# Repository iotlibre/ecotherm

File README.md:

ecoTherm
==========
ecoThermal esta diseñado para medir la energía térmica de una instalación que disponga de uno o varios circuitos de agua a diferentes temperaturas. Este dispositivo esta diseñado para medir:

* Temperatura mediante sondas del tipo 18b20
* Caudal a través de pulsos proporcionados por contadores de agua
* Valores analógicos tanto de voltaje como de corriente. 

Las medias se toman cada segundo haciendo una media de estos valores para cada periodo de reporte en el que el valor es proporcionado.

ecoThermal se puede instalar sobre carril DIN a una distancia que permita la comunicación con las sondas disponibles en la instalación. En un edificio podemos tener tantos dispositivos como sean necesarios y el servidor los integrará en la misma instalación sin necesidad de configuraciones adicionales o cambios en el Firmware. La comunicación se hace mediante wifi por lo que no es necesario el cableado de datos al equipo solamente es preciso que esté dentro de la cobertura de la red wifi del edificio.

Para el uso de ecoThermal, no son necesarios conocimientos de informática aunque todos los desarrollos y el hardware están hechos bajo licencias libres lo que permite la modificación y mejora de las funcionalidades.

.. image:: ./imagenes/ecothermal_board.png

Principales características
---------------------------
* 15 entradas configurables para cada tipo de sensor
* Admite hasta 28 sondas de temperatura repartidas en 7 buses
* Es posible integrar hasta 15 medidas de caudal
* Puede medir hasta 8 Valores analógicos
* Precisión en las medida de temperatura: ± 0,5 °C
* La precisión de las medidas analógicas depende de las sondas utilizadas.
* La precisión de las medias de caudal corresponde a los medidores implementados
* Comunicación a Internet se hace por WIFI local
* Configurable vía Web
* Estandard: IEEE 802.11 b/g/n
* Alimentación a 220 voltios de corriente alterna. Rango: 85 ~ 264VAC
* Montaje en carril din
* La PCB integra un Arduino nano con el ESP8266 12E
* Compatible con el servidor IoE

Puesta a punto
--------------
La puesta a punto de ecoThermal consta de tres partes:

* La configuración del hardware
* El firmware de Arduino
* La configuración en la instalación

La configuración del hardware
~~~~~~~~~~~~~~~~~~~~~~~~~~~~~
El hardware por defecto esta preparado para 8 entradas analógicas, 3 caudales y 16 sondas de temperatura repartidas en 4 buses. Sin embargo esta configuración se puede modificar cambiando los componentes de superficie de la PCB hasta la combinación de medidas que nos se adapte mas al proyecto.

El firmware de Arduino
~~~~~~~~~~~~~~~~~~~~~~
El firmware que esta cargado, por defecto, en el Arduino nano funciona correctamente con la configuración, del hardware, por defecto. En el caso de cambiar el hardware también es necesario cambiar el firmware del Arduino integrado en la PCB y que se puede encontrar en el código fuente

La configuración en la instalación
~~~~~~~~~~~~~~~~~~~~~~~~~~~~~~~~~~
En este punto se definen los parámetros del servidor de destino y la wifi local a la que va a estar conectado el dispositivo. Con este fin, la primera vez que se ponga en servicio el ESP y siempre que no encuentre la WIFI configurada, el ESP 8266 12E creará su propio punto de acceso, su propia red WIFI. Conectándose a cualquier dirección a través de este punto de acceso nos aparecerá la página de configuración del ESP. Tengase en cuenta que una vez configurado el ESP y conectado a una red WIFI el router le asignará una única dirección IP a la que será necesario acceder para cambiar la configuración

Código fuente
~~~~~~~~~~~~~
El código del firmware y la documentación del hardware se puede encontrar en `repositorio <https://github.com/iotlibre/ecoThermal>`_

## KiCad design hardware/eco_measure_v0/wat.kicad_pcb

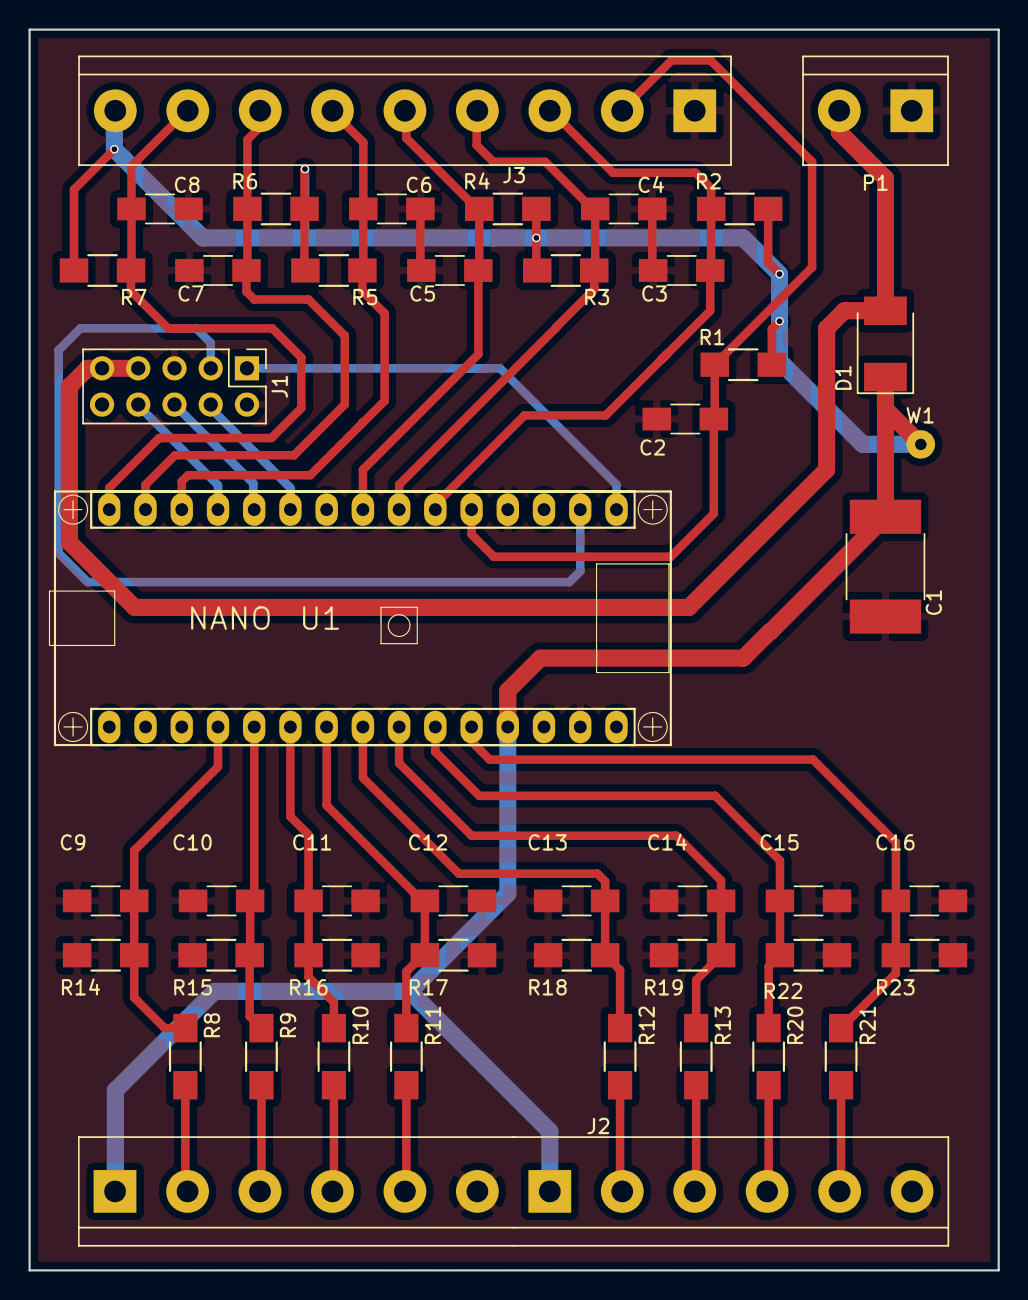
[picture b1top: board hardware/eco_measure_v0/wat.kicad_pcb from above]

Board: 2 copper layers, 67.9 x 87.0 mm, 46 parts (0 on the bottom side), 31 nets.

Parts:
C1: 10uF; C_2220_HandSoldering
C2, C3, C4, C5, C6, C7, C8, C9, C10, C11, C12, C13, C14, C15, C16: 100nF; C_1206_HandSoldering
D1: schottky; D_2114
J1: Conn_02x05_Odd_Even; Pin_Header_Straight_2x05_Pitch2.54mm_onsar
J2: Conn_01x12; TerminalBlock_bornier-12_P5.08mm
J3: Conn_01x09; TerminalBlock_bornier-9_P5.08mm
P1: V_IN; TerminalBlock_bornier-2_P5.08mm
R1, R2, R3, R4, R5, R6, R7, R8, R9, R10, R11, R12, R13, R14, R15, R16, R17, R18, R19, R20, R21, R22, R23: 10k; R_1206_HandSoldering
U1: NANO; arduino_nano
W1: +5V; SolderWirePad_single_0-8mmDrill

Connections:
/A0: C9.1, R8.1, R14.2, U1.19
/A1: C10.1, R9.1, R15.2, U1.20
/A2: C11.1, R10.1, R16.2, U1.21
/A3: C12.1, R11.1, R17.2, U1.22
/A4: C13.1, R12.1, R18.2, U1.23
/A5: C14.1, R13.1, R19.2, U1.24
/A6: C15.1, R20.1, R22.2, U1.25
/A7: C16.1, R21.1, R23.2, U1.26
/D2: C2.1, J3.2, R1.1, U1.5
/D3: C3.1, J3.3, R2.1, U1.6
/D4: C4.1, J3.4, R3.1, U1.7
/D5: C5.1, J3.5, R4.1, U1.8
/D7: J1.4, U1.10
/D8: J1.6, U1.11
/D9: J1.8, U1.12
/D10: C6.1, J3.6, R5.1, U1.13
/D11: C7.1, J3.7, R6.1, U1.14
/D12: C8.1, J3.8, R7.1, U1.15
/ard_rx: J1.3, U1.2
/ard_tx: J1.1, U1.1
/jA0: J2.2, R8.2
/jA1: J2.3, R9.2
/jA2: J2.4, R10.2
/jA3: J2.5, R11.2
/jA4: J2.8, R12.2
/jA5: J2.9, R13.2
/jA6: J2.10, R20.2
/jA7: J2.11, R21.2
/vcc_5v: D1.2, J1.7, J1.9, P1.2
GND: C1.2, C2.2, C3.2, C4.2, C5.2, C6.2, C7.2, C8.2, C9.2, C10.2, C11.2, C12.2, C13.2, C14.2, C15.2, C16.2, J1.2, J1.5, J2.6, J2.12, J3.1, P1.1, R14.1, R15.1, R16.1, R17.1, R18.1, R19.1, R22.1, R23.1, U1.4, U1.29
VCC: C1.1, D1.1, J2.1, J2.7, J3.9, R1.2, R2.2, R3.2, R4.2, R5.2, R6.2, R7.2, U1.27, W1.1

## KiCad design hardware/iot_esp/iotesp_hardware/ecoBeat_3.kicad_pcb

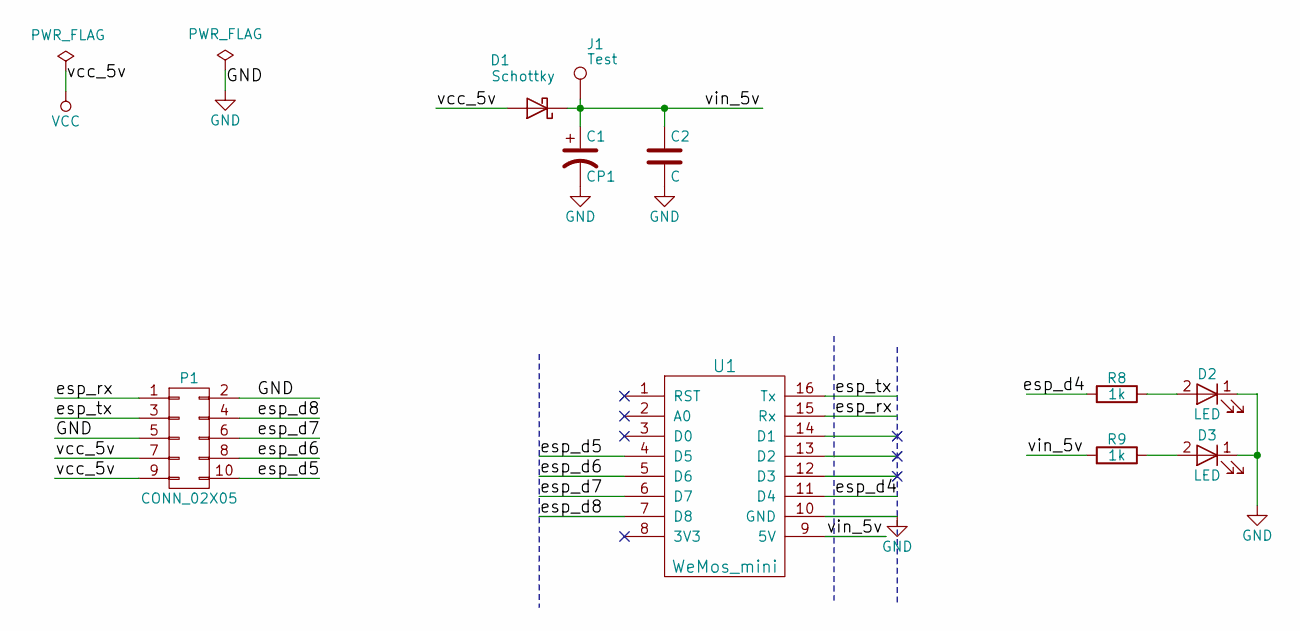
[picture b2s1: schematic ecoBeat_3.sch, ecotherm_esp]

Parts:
C1: CP1; C_2220_HandSoldering
C2: C; C_1206_HandSoldering
D1: Schottky; D_2114
D2, D3: LED; LED_D3.0mm
J1: Test; SolderWirePad_single_0-8mmDrill
P1: CONN_02X05; D1_mini_board
R8, R9: 1k; R_1206_HandSoldering
U1: WeMos_mini; D1_mini_board_oscar

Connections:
/esp_d4: R8.2, U1.11 (D4)
/esp_d5: P1.10, U1.4 (D5)
/esp_d6: P1.8, U1.5 (D6)
/esp_d7: P1.6, U1.6 (D7)
/esp_d8: P1.4, U1.7 (D8)
/esp_rx: P1.1, U1.15 (Rx)
/esp_tx: P1.3, U1.16 (Tx)
/vin_5v: C1.1, C2.1, D1.1 (K), J1.1, R9.2, U1.9 (5V)
GND: C1.2, C2.2, D2.1 (K), D3.1 (K), P1.2, P1.5, U1.10 (GND)
unnamed: D2.2 (A), R8.1
unnamed: D3.2 (A), R9.1
VCC: D1.2 (A), P1.7, P1.9

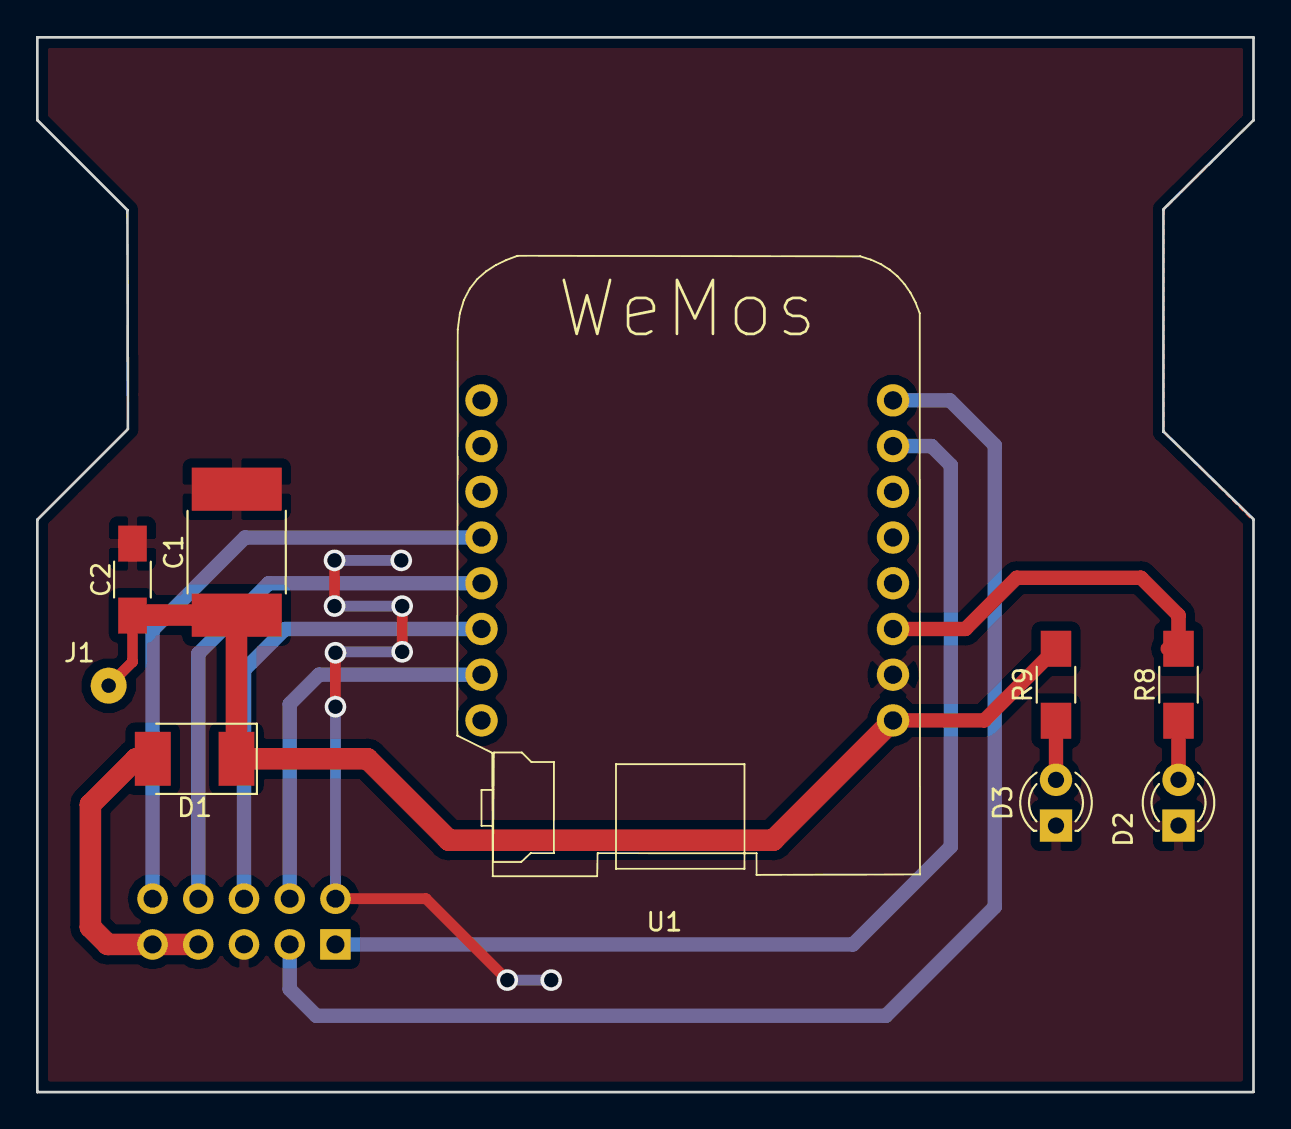
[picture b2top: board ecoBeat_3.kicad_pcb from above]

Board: 2 copper layers, 67.6 x 58.6 mm, 10 parts (1 on the bottom side), 12 nets.

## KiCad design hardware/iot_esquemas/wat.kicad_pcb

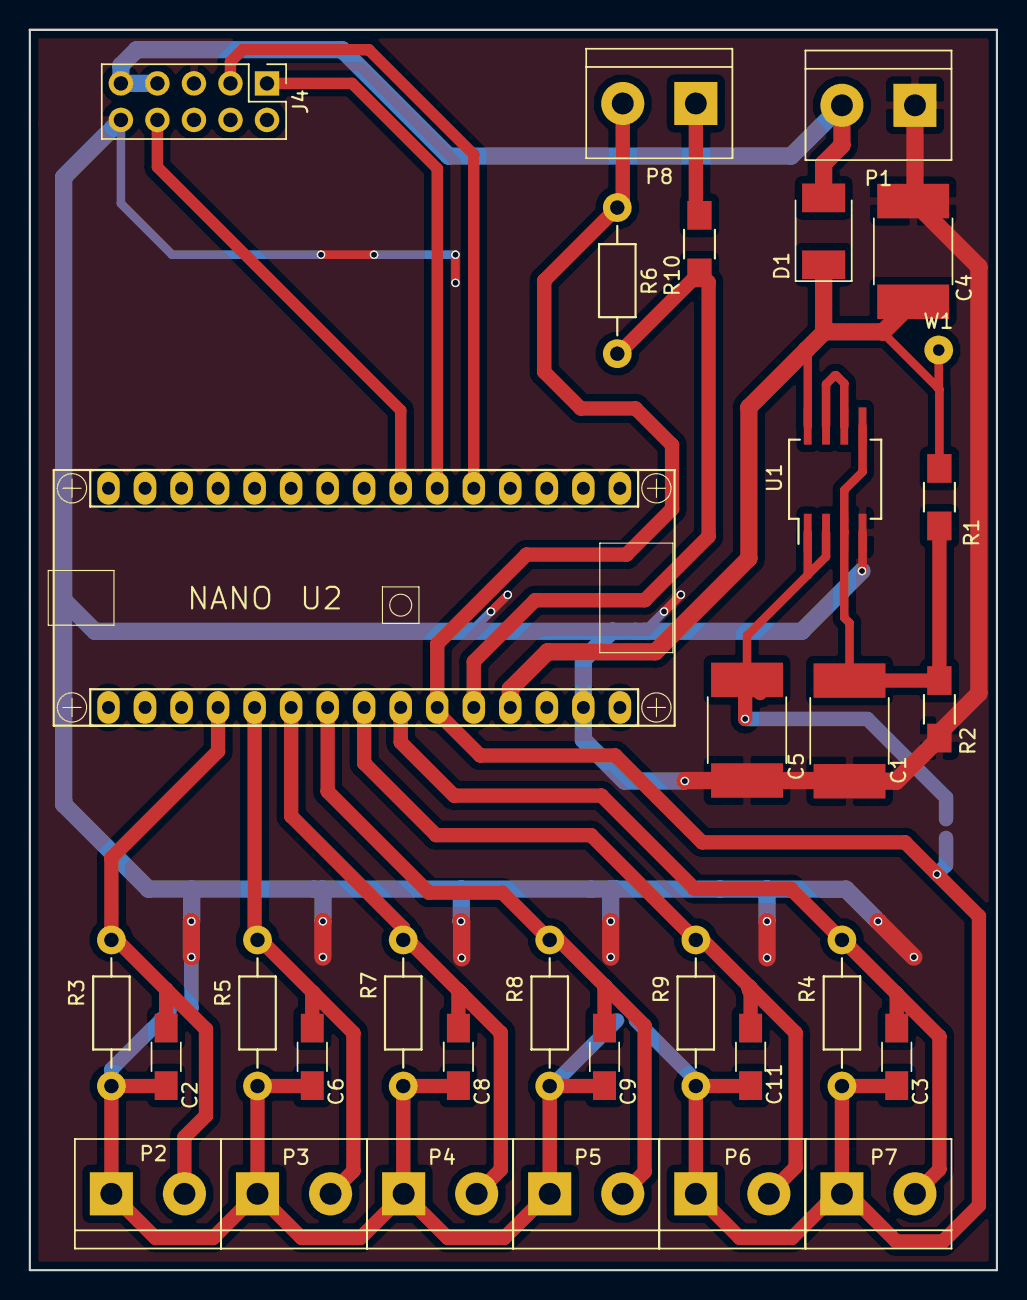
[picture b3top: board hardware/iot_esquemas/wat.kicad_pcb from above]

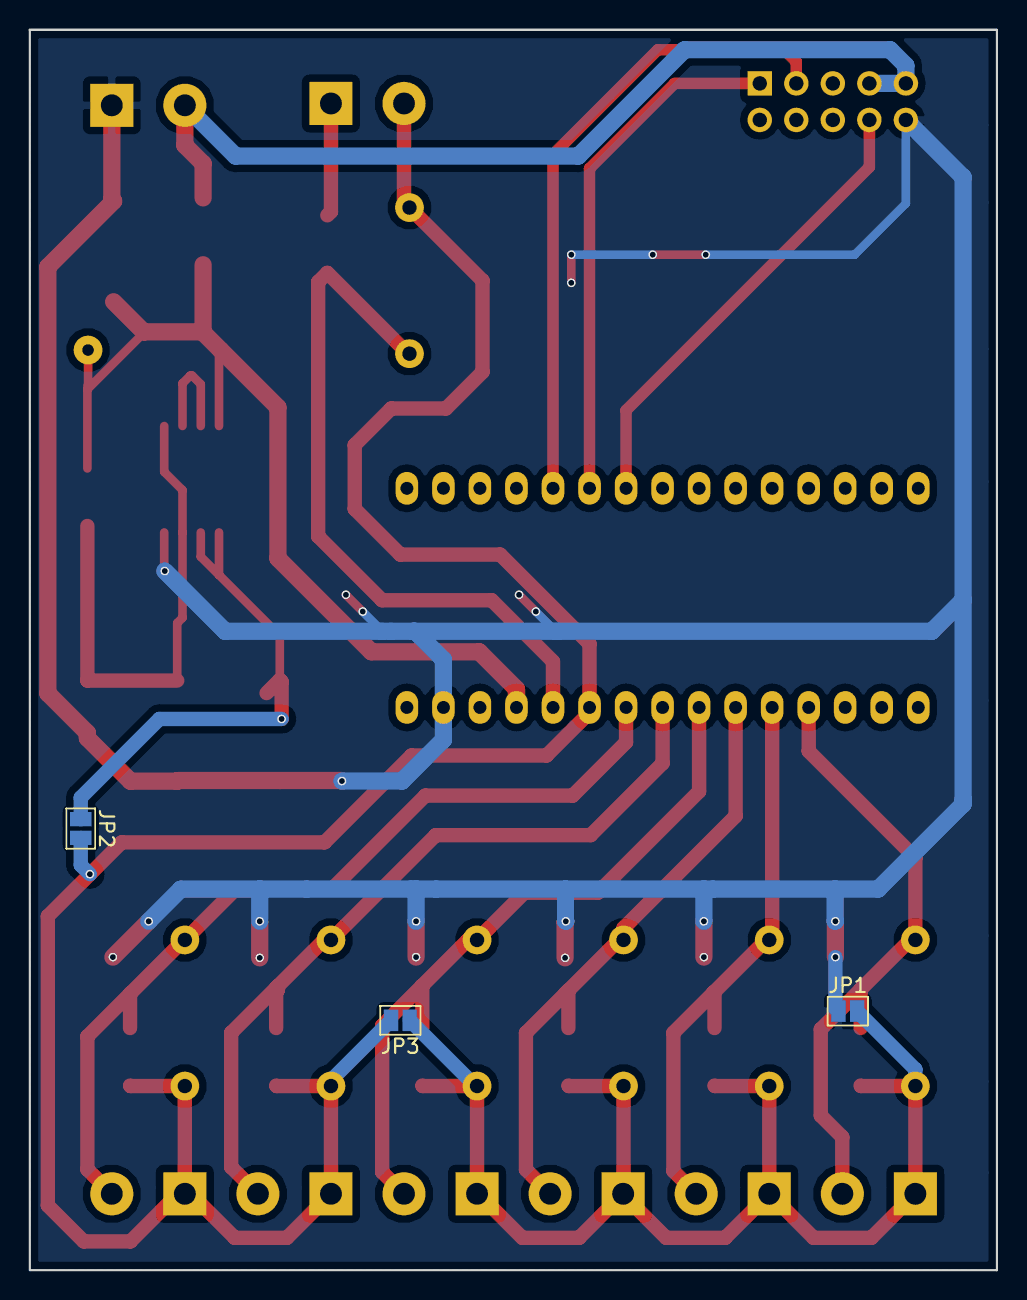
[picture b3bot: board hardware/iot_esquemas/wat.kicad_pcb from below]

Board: 2 copper layers, 67.2 x 86.2 mm, 35 parts (3 on the bottom side), 19 nets.

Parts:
C1, C4, C5: 10uF; C_2220_HandSoldering
C2, C3, C6, C8, C9, C11: 100nF; C_1206_HandSoldering
D1: schottky; D_2114
J4: Conn_02x05_Odd_Even; Pin_Header_Straight_2x05_Pitch2.54mm_onsar
JP1, JP2, JP3: Jumper_2_Open; SolderJumper-2_P1.3mm_Open_Pad1.0x1.5mm
P1: V_IN; TerminalBlock_bornier-2_P5.08mm
P2: PINZA_1; TerminalBlock_bornier-2_P5.08mm
P3: PINZA_2; TerminalBlock_bornier-2_P5.08mm
P4: PINZA_3; TerminalBlock_bornier-2_P5.08mm
P5: PINZA_4; TerminalBlock_bornier-2_P5.08mm
P6: PINZA_5; TerminalBlock_bornier-2_P5.08mm
P7: PINZA_6; TerminalBlock_bornier-2_P5.08mm
P8: PINZA_7; TerminalBlock_bornier-2_P5.08mm
R1, R2: 4K7; R_1206_HandSoldering
R3, R4, R5, R7, R8, R9: 10k; Resistor_Horizontal_RM10mm
R6: 1k; Resistor_Horizontal_RM10mm
R10: 10k; R_1206_HandSoldering
U1: LM358; SO-8_5.3x6.2mm_Pitch1.27mm
U2: NANO; arduino_nano
W1: +5V; SolderWirePad_single_0-8mmDrill

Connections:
/ard_d4: J4.8, U2.7
/ard_rx: J4.3, U2.5
/ard_tx: J4.1, U2.6
/intensidad_1: C2.1, P2.2, R3.1, U2.19
/intensidad_2: C6.1, P3.2, R5.1, U2.20
/intensidad_3: C8.1, P4.2, R7.1, U2.21
/intensidad_4: C9.1, P5.2, R8.1, U2.22
/intensidad_5: C11.1, P6.2, R9.1, U2.23
/intensidad_6: C3.1, P7.2, R4.1, U2.24
/v_25: C1.1, R1.2, R2.1, U1.3, U1.5
/v_comun_0: C2.2, C6.2, C8.2, C9.2, JP1.2, JP3.1, P2.1, P3.1, P4.1, P5.1, R3.2, R5.2, R7.2, R8.2
/v_comun_1: C3.2, C11.2, JP2.2, JP3.2, P6.1, P7.1, P8.2, R4.2, R6.2, R9.2, U2.25
/v_op: C5.1, JP2.1, U1.1, U1.2
/vcc_5v: D1.2, J4.7, J4.9, P1.2
/voltage_1: R6.1, R10.1, U2.26
GND: C1.2, C4.2, C5.2, J4.5, J4.10, JP1.1, P1.1, R2.2, U1.4, U2.29
unnamed: P8.1, R10.2
unnamed: U1.6, U1.7
VCC: C4.1, D1.1, R1.1, U1.8, U2.27, W1.1

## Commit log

2021-05-23 first operative version
2021-07-08 bug variable de tx rebasda
2021-09-11 v.1.0 Stable software and hardware
2021-09-12 iot-esp hw v3: side ventilation
2021-09-12 Rename README.md to README.rst
2021-10-12 raspberry compatible connector
2021-10-16 introductory document in english
2021-10-17 new images
2021-10-17 minor
2021-10-24 images to the readme
2022-05-26 Create licence
2022-06-29 numero de samples aumentado
2022-07-08 bug:temperaturas incorrectas por debajo de 0 grados
